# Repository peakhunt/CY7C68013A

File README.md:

# CY7C68013A
I have a blue chinese board of this. It must be so called FX2LP board.  
It is an interesting old technology based on ancient 8051 core and powerful USB 2.0 High Speed capability.  

## to build
first install the following packages  
  
sudo apt install sdcc cycfx2prog  
sudo apt install fxload  

then
* make
* sudo make run  
  to download into ram and run
* sudo make program  
  to flash to eeprom  
  
You might have to wrestle with EEPROM A0 jumper on the board.  
In my case, A0 is pulled up to 3V3 via 10K resistor by default, which makes sense since EEPOM is a large one.  
And the jumper actually connects A0 pin to GND.  
But most documents in the internet say the opposite.  
  
And SDCC is not that bad.  

## Something to note
* RDY0/RDY1 pins are mislabled  
  RDY0 is actually RDY1 and vice versa  
  Check your board with multimeter or you might have to waste a lot of time to make slave fifo work

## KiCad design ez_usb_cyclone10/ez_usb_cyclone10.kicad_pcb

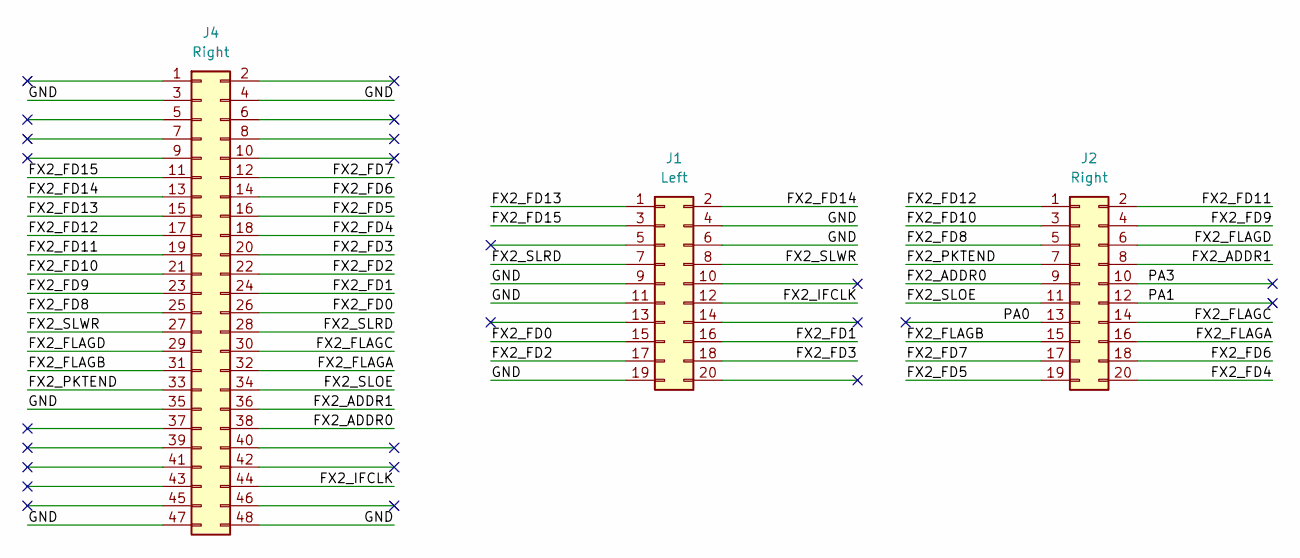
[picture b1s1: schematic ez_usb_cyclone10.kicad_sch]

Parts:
J1: Left; PinHeader_2x10_P2.54mm_Vertical
J2: Right; PinHeader_2x10_P2.54mm_Vertical
J4: Right; PinHeader_2x24_P2.54mm_Vertical

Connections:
/FX2_ADDR0: J2.9, J4.38
/FX2_ADDR1: J2.8, J4.36
/FX2_FD0: J1.15, J4.26
/FX2_FD1: J1.16, J4.24
/FX2_FD2: J1.17, J4.22
/FX2_FD3: J1.18, J4.20
/FX2_FD4: J2.20, J4.18
/FX2_FD5: J2.19, J4.16
/FX2_FD6: J2.18, J4.14
/FX2_FD7: J2.17, J4.12
/FX2_FD8: J2.5, J4.25
/FX2_FD9: J2.4, J4.23
/FX2_FD10: J2.3, J4.21
/FX2_FD11: J2.2, J4.19
/FX2_FD12: J2.1, J4.17
/FX2_FD13: J1.1, J4.15
/FX2_FD14: J1.2, J4.13
/FX2_FD15: J1.3, J4.11
/FX2_FLAGA: J2.16, J4.32
/FX2_FLAGB: J2.15, J4.31
/FX2_FLAGC: J2.14, J4.30
/FX2_FLAGD: J2.6, J4.29
/FX2_IFCLK: J1.12, J4.44
/FX2_PKTEND: J2.7, J4.33
/FX2_SLOE: J2.11, J4.34
/FX2_SLRD: J1.7, J4.28
/FX2_SLWR: J1.8, J4.27
/GND: J1.4, J1.6, J1.9, J1.11, J1.19, J4.3, J4.4, J4.35, J4.47, J4.48
/PA0: J2.13
/PA1: J2.12
/PA3: J2.10

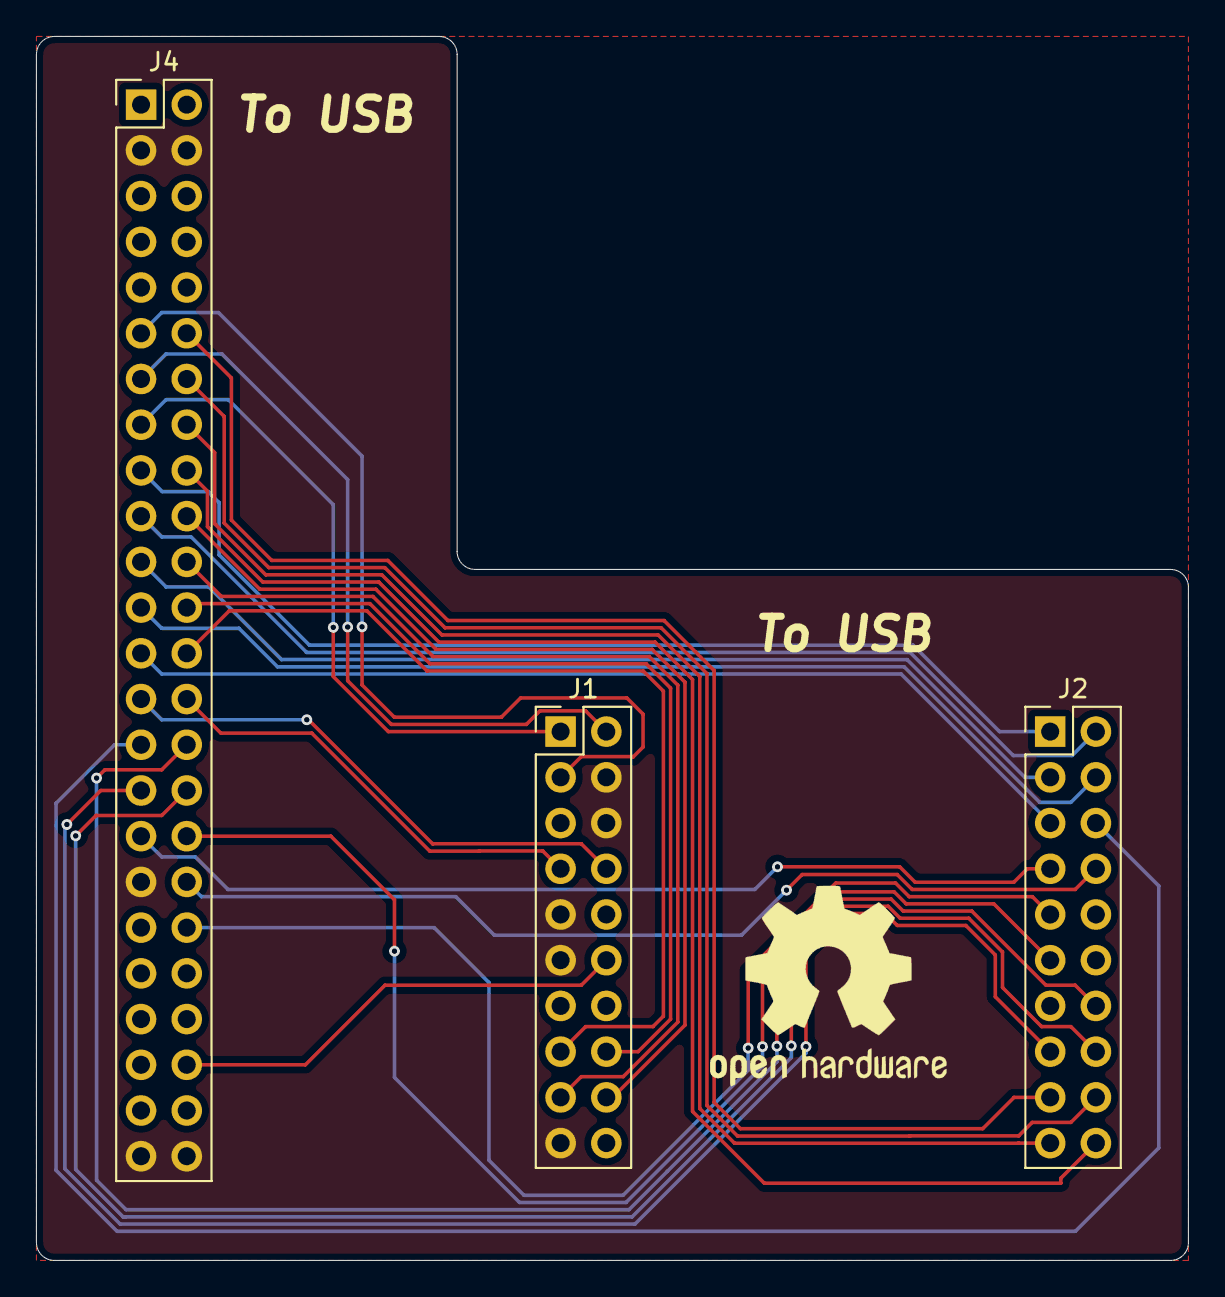
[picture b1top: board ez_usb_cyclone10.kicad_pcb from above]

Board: 2 copper layers, 64.0 x 68.0 mm, 3 parts (0 on the bottom side), 28 nets.

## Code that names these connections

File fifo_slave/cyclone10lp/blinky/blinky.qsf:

# -------------------------------------------------------------------------- #
#
# Copyright (C) 2025  Altera Corporation. All rights reserved.
# Your use of Altera Corporation's design tools, logic functions 
# and other software and tools, and any partner logic 
# functions, and any output files from any of the foregoing 
# (including device programming or simulation files), and any 
# associated documentation or information are expressly subject 
# to the terms and conditions of the Altera Program License 
# Subscription Agreement, the Altera Quartus Prime License Agreement,
# the Altera IP License Agreement, or other applicable license
# agreement, including, without limitation, that your use is for
# the sole purpose of programming logic devices manufactured by
# Altera and sold by Altera or its authorized distributors.  Please
# refer to the Altera Software License Subscription Agreements 
# on the Quartus Prime software download page.
#
# -------------------------------------------------------------------------- #
#
# Quartus Prime
# Version 25.1std.0 Build 1129 10/21/2025 SC Lite Edition
# Date created = 13:38:20  May 12, 2026
#
# -------------------------------------------------------------------------- #
#
# Notes:
#
# 1) The default values for assignments are stored in the file:
#		blinky_assignment_defaults.qdf
#    If this file doesn't exist, see file:
#		assignment_defaults.qdf
#
# 2) Intel recommends that you do not modify this file. This
#    file is updated automatically by the Quartus Prime software
#    and any changes you make may be lost or overwritten.
#
# -------------------------------------------------------------------------- #


set_global_assignment -name FAMILY "Cyclone 10 LP"
set_global_assignment -name DEVICE 10CL006YE144C8G
set_global_assignment -name TOP_LEVEL_ENTITY blinky_top
set_global_assignment -name ORIGINAL_QUARTUS_VERSION 25.1STD.0
set_global_assignment -name PROJECT_CREATION_TIME_DATE "13:38:20  MAY 12, 2026"
set_global_assignment -name LAST_QUARTUS_VERSION "25.1std.0 Lite Edition"
set_global_assignment -name PROJECT_OUTPUT_DIRECTORY output_files
set_global_assignment -name MIN_CORE_JUNCTION_TEMP 0
set_global_assignment -name MAX_CORE_JUNCTION_TEMP 85
set_global_assignment -name ERROR_CHECK_FREQUENCY_DIVISOR 1
set_global_assignment -name NOMINAL_CORE_SUPPLY_VOLTAGE 1.2V
set_global_assignment -name POWER_PRESET_COOLING_SOLUTION "23 MM HEAT SINK WITH 200 LFPM AIRFLOW"
set_global_assignment -name POWER_BOARD_THERMAL_MODEL "NONE (CONSERVATIVE)"
set_global_assignment -name PARTITION_NETLIST_TYPE SOURCE -section_id Top
set_global_assignment -name PARTITION_FITTER_PRESERVATION_LEVEL PLACEMENT_AND_ROUTING -section_id Top
set_global_assignment -name PARTITION_COLOR 16764057 -section_id Top
set_global_assignment -name TIMING_ANALYZER_MULTICORNER_ANALYSIS ON
set_global_assignment -name NUM_PARALLEL_PROCESSORS 4
set_location_assignment PIN_98 -to leds[0]
set_instance_assignment -name IO_STANDARD "3.3-V LVTTL" -to rst_n
set_location_assignment PIN_91 -to clk_50
set_location_assignment PIN_99 -to leds[1]
set_location_assignment PIN_100 -to leds[2]
set_location_assignment PIN_101 -to leds[3]
set_location_assignment PIN_89 -to rst_n
set_global_assignment -name ENABLE_OCT_DONE OFF
set_global_assignment -name ENABLE_CONFIGURATION_PINS OFF
set_global_assignment -name ENABLE_BOOT_SEL_PIN OFF
set_global_assignment -name USE_CONFIGURATION_DEVICE OFF
set_global_assignment -name CRC_ERROR_OPEN_DRAIN OFF
set_global_assignment -name CYCLONEII_RESERVE_NCEO_AFTER_CONFIGURATION "USE AS REGULAR IO"
set_global_assignment -name OUTPUT_IO_TIMING_NEAR_END_VMEAS "HALF VCCIO" -rise
set_global_assignment -name OUTPUT_IO_TIMING_NEAR_END_VMEAS "HALF VCCIO" -fall
set_global_assignment -name OUTPUT_IO_TIMING_FAR_END_VMEAS "HALF SIGNAL SWING" -rise
set_global_assignment -name OUTPUT_IO_TIMING_FAR_END_VMEAS "HALF SIGNAL SWING" -fall
set_instance_assignment -name IO_STANDARD "3.3-V LVTTL" -to clk_50
set_global_assignment -name STRATIX_DEVICE_IO_STANDARD "3.3-V LVTTL"
set_global_assignment -name SDC_FILE blinky_top.sdc
set_global_assignment -name VHDL_FILE blinky_top.vhd
set_global_assignment -name VHDL_FILE counter.vhd
set_global_assignment -name VHDL_FILE reset_sync.vhd
set_global_assignment -name VHDL_FILE toggle.vhd
set_global_assignment -name QIP_FILE sys_pll.qip
set_location_assignment PIN_103 -to fx2_addr0
set_location_assignment PIN_106 -to fx2_addr1
set_instance_assignment -name IO_STANDARD "3.3-V LVTTL" -to fx2_addr0
set_instance_assignment -name IO_STANDARD "3.3-V LVTTL" -to fx2_addr1
set_location_assignment PIN_23 -to fx2_ifclk
set_instance_assignment -name IO_STANDARD "3.3-V LVTTL" -to fx2_ifclk
set_location_assignment PIN_111 -to fx2_sloe
set_instance_assignment -name IO_STANDARD "3.3-V LVTTL" -to fx2_sloe
set_location_assignment PIN_112 -to fx2_pktend
set_instance_assignment -name IO_STANDARD "3.3-V LVTTL" -to fx2_pktend
set_location_assignment PIN_113 -to fx2_flaga
set_instance_assignment -name IO_STANDARD "3.3-V LVTTL" -to fx2_flaga
set_location_assignment PIN_114 -to fx2_flagb
set_instance_assignment -name IO_STANDARD "3.3-V LVTTL" -to fx2_flagb
set_location_assignment PIN_115 -to fx2_flagc
set_instance_assignment -name IO_STANDARD "3.3-V LVTTL" -to fx2_flagc
set_location_assignment PIN_119 -to fx2_flagd
set_instance_assignment -name IO_STANDARD "3.3-V LVTTL" -to fx2_flagd
set_location_assignment PIN_120 -to fx2_slrd
set_location_assignment PIN_121 -to fx2_slwr
set_instance_assignment -name IO_STANDARD "3.3-V LVTTL" -to fx2_slrd
set_instance_assignment -name IO_STANDARD "3.3-V LVTTL" -to fx2_slwr
set_location_assignment PIN_124 -to fx2_fd[0]
set_instance_assignment -name IO_STANDARD "3.3-V LVTTL" -to fx2_fd[0]
set_location_assignment PIN_126 -to fx2_fd[1]
set_instance_assignment -name IO_STANDARD "3.3-V LVTTL" -to fx2_fd[1]
set_location_assignment PIN_128 -to fx2_fd[2]
set_instance_assignment -name IO_STANDARD "3.3-V LVTTL" -to fx2_fd[2]
set_location_assignment PIN_132 -to fx2_fd[3]
set_instance_assignment -name IO_STANDARD "3.3-V LVTTL" -to fx2_fd[3]
set_location_assignment PIN_135 -to fx2_fd[4]
set_location_assignment PIN_137 -to fx2_fd[5]
set_location_assignment PIN_141 -to fx2_fd[6]
set_location_assignment PIN_143 -to fx2_fd[7]
set_instance_assignment -name IO_STANDARD "3.3-V LVTTL" -to fx2_fd[4]
set_instance_assignment -name IO_STANDARD "3.3-V LVTTL" -to fx2_fd[5]
set_instance_assignment -name IO_STANDARD "3.3-V LVTTL" -to fx2_fd[6]
set_instance_assignment -name IO_STANDARD "3.3-V LVTTL" -to fx2_fd[7]
set_location_assignment PIN_125 -to fx2_fd[8]
set_location_assignment PIN_127 -to fx2_fd[9]
set_location_assignment PIN_129 -to fx2_fd[10]
set_location_assignment PIN_133 -to fx2_fd[11]
set_location_assignment PIN_136 -to fx2_fd[12]
set_location_assignment PIN_138 -to fx2_fd[13]
set_location_assignment PIN_142 -to fx2_fd[14]
set_location_assignment PIN_144 -to fx2_fd[15]
set_instance_assignment -name IO_STANDARD "3.3-V LVTTL" -to fx2_fd[15]
set_instance_assignment -name IO_STANDARD "3.3-V LVTTL" -to fx2_fd[14]
set_instance_assignment -name IO_STANDARD "3.3-V LVTTL" -to fx2_fd[13]
set_instance_assignment -name IO_STANDARD "3.3-V LVTTL" -to fx2_fd[12]
set_instance_assignment -name IO_STANDARD "3.3-V LVTTL" -to fx2_fd[11]
set_instance_assignment -name IO_STANDARD "3.3-V LVTTL" -to fx2_fd[10]
set_instance_assignment -name IO_STANDARD "3.3-V LVTTL" -to fx2_fd[9]
set_instance_assignment -name IO_STANDARD "3.3-V LVTTL" -to fx2_fd[8]
set_instance_assignment -name PARTITION_HIERARCHY root_partition -to | -section_id Top

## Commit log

2026-05-10 changed d2 led blinking mechnism
2026-05-10 blocking reenumerate
2026-05-10 slowing down t1 blinking rate
2026-05-10 adding humble readme
2026-05-10 always type as I get older and older
2026-05-10 holy markdown
2026-05-10 adding gitignore
2026-05-10 removing useless stuffs
2026-05-10 hate tabs
2026-05-10 readme update
2026-05-11 stupid bit bug
2026-05-11 dumb
2026-05-11 hid example using tm1638
2026-05-11 dont like tabs
2026-05-11 adding experimental fast code that can't handle fullspeed case
2026-05-11 removing debug dump
2026-05-12 adding trm doc for ez-usb
2026-05-12 working on fpga demo project
2026-05-12 fpga doc update
2026-05-12 adding fpga makefile for convenience
2026-05-13 fixing sdc for annoything timing violation
2026-05-13 working on bulk out ep test with fpga
2026-05-15 bulk out transfer fifo slave setup
2026-05-15 libusb test code
2026-05-15 fx2lp synchronous slave fifo interface
2026-05-15 adding code commnet
2026-05-15 code comment
2026-05-15 comment change
2026-05-16 fixing weird 2 byte problem on fpga side
2026-05-16 fixing bus timing error in reading from dcfifo
2026-05-16 changing max power back to 100mA
2026-05-16 code clenaup
2026-05-16 fixed makefile
2026-05-16 makefile fix for old blinky demo
2026-05-18 adding kicad design to escape from wire hell
2026-05-18 readjusting blink basis with new kicad board design
2026-05-18 cyclone10 chinese board doc update
2026-05-18 removing unnecessary files
